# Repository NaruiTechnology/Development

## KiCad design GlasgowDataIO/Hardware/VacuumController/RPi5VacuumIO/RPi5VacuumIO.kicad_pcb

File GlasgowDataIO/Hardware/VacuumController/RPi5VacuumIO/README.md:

# RPi5 Vacuum Controller I/O board (rev A.1)

This is the interface board between a **Raspberry Pi** and the **FEI DB235 vacuum system**. The controller SBC is a **Raspberry Pi 4 Model B** (see `glasgow_service/docs/rpi-vacuum-shopping-list.md`); the board works unchanged on a **Raspberry Pi 5**, because it uses only the 40-pin header and every pin it uses has the same function on both models. The "RPi5" in the name is historical.

The board connects:

- the four pumps shown on the SBC Vacuum Controller dashboard: `MechanicalVacuumPump`, `TurboVacuumPump`, and the UH stage `UHVacuumPump_1` / `UHVacuumPump_2` (turbomolecular pumps);
- the vacuum gauges;
- the valves and pneumatic cylinders;
- the high-voltage permissive;
- the E-stop.

Step-by-step device wiring is in **[WIRING.md](WIRING.md)**.

The Pi runs `glasgow_service.sbc_vacuum_app`. This board gives it isolated, fail-safe I/O. The service talks to it through `glasgow_service/vacuum_io_board.py`. The whole board, the Pi and the DB235 are emulated in `glasgow_service.emulation`, so the controller can be tested without hardware (`python -m glasgow_service.emulation commission`; see `glasgow_service/docs/vacuum-emulator.md`).

```
 Raspberry Pi 4B/5 ─40-way ribbon─> J3 ─┬─ I2C ─ MCP23017 0x20 ─┬─ ULN2803A ─ K1..K8 relays  ─> pump / HV permissive contacts
                                       │                       └─ AO3400A x8 ─ V1..V8        ─> 24 V valve & cylinder solenoids
                                       ├─ I2C ─ MCP23017 0x21 ─── TLP291-4 x4 ─ DI1..DI16    <─ pump status, valve/cylinder switches
                                       ├─ I2C ─ ADS1115 x2 ─────── 68k/22k ─── AI1..AI8      <─ 0-10 V gauges, pump analog outputs
                                       ├─ UART0 ─ MAX3485 ──────── RS-485                    <─> turbo / gauge controller
                                       ├─ UART4 ─ MAX3232 ──────── RS-232                    <─> gauge controller
                                       └─ GPIO19 heartbeat ─ charge pump ─ K10 ─┐
 24 VDC ─ fuse ─ K9 (E-stop loop J2) ─ +24V_ESTOP ──────────────────────────────┴─ +24V_SAFE ─> solenoids, relay coils
```

## Channel counts

| Function | Channels | Hardware |
|---|---|---|
| Relay outputs | 8 × SPDT, 10 A contacts, COM/NO/NC on pluggable terminals | Omron G5LE-1 24 V, driven by ULN2803A |
| Solenoid outputs | 8 × 24 V low-side switches, up to 1 A each (fused 4 A total), flyback diodes, LED per channel | AO3400A MOSFETs |
| Digital inputs | 16 × opto-isolated 24 V, 4 groups with separate commons, LED per channel | TLP291-4 |
| Analog inputs | 8 × 0–10.5 V, 16-bit, clamped, about 90 Hz filter | ADS1115 × 2 |
| Serial | 1 × RS-485 (termination jumper, fail-safe bias, TVS); 1 × RS-232 | MAX3485, MAX3232 |
| Safety | E-stop loop input, heartbeat watchdog, rail status readback to the Pi | K9, K10, TLP291-4 |

## Channel map (matches the software)

The pumps, their order and their A/B channels are exactly those of `glasgow_service` and `vacuumSystem.json`, as shown on the SBC Vacuum Controller dashboard. The cascade is: `MechanicalVacuumPump` → `TurboVacuumPump` → the UH pump group (`UHVacuumPump_1`, `UHVacuumPump_2`).

| Software device | Output (A) → relay | Ready input (B) → DI | Fault input | Gauge (numeric value) | Speed / analog | Serial |
|---|---|---|---|---|---|---|
| `MechanicalVacuumPump` | A0 → **K1** | B0 → **DI1** (running / pressure OK) | DI5 | AI1 (fore-line Pirani) | – | – |
| `TurboVacuumPump` | A1 → **K2** | B1 → **DI2** (at normal speed) | DI6 | AI2 (chamber gauge) | AI5 | RS-485 J4, address 1 |
| `UHVacuumPump_1` (turbo) | A2 → **K3** | B2 → **DI3** (at normal speed) | DI7 | AI3 | AI6 | RS-485 J4, address 2 |
| `UHVacuumPump_2` (turbo) | A3 → **K4** | B3 → **DI4** (at normal speed) | DI8 | AI4 | AI7 | RS-485 J4, address 3 |
| `HighVoltageTransformer` | A4 → **K5** (HV permissive) | – | – | – | – | – |

The same map is printed on the back silkscreen. It is also in `GlasgowDataIO/Json/vacuumSystem.rpi5-io.example.json`.

### Remaining channels

| Channel | Suggested use |
|---|---|
| K6 | Full-range / cold-cathode gauge HV on |
| K7, K8 | Spare (for example an alarm beacon) |
| V1 | Roughing / fore-line valve (mechanical pump → turbo fore-lines) |
| V2 | Chamber gate valve (TurboVacuumPump inlet), pneumatic |
| V3 | Vent valve (dry N2) |
| V4 | UH stage isolation valve 1 (UHVacuumPump_1 inlet), pneumatic |
| V5 | UH stage isolation valve 2 (UHVacuumPump_2 inlet), pneumatic |
| V6 | Bypass / chamber roughing valve |
| V7 | Pneumatic cylinder (for example a load-lock or clamp) |
| V8 | Spare |
| DI9, DI10 | V2 open / closed position switches |
| DI11, DI12 | V4 open / closed position switches |
| DI13 | Chamber door closed |
| DI14 | Compressed air OK |
| DI15 | N2 vent gas OK |
| DI16 | Cooling water flow OK |
| AI8 | Spare |

The controller software sequences the pumps and the HV permissive (A0–A4, B0–B3, the per-pump gauges), and acts on the fault inputs (`SBC.Faults`), the E-stop and output-rail status (GPIO5/6), the keep-alive and expander resets. All 16 inputs, the relays and the solenoids are reported in `GET /vacuum` → `board`. The per-pump isolation valves V1, V2, V4 and V5 are driven by the controller (`SBC.Valves`: open exactly while that pump is ready, see `glasgow_service/docs/sbc-vacuum-controller.md`). The vent, bypass, cylinder and utility channels are wired and readable, but not sequenced yet.

## Fail-safe behaviour

| Condition | Result |
|---|---|
| Pi off, booting, or the service not started | GPIO22 is low, so both MCP23017s are held in reset. Every driver input is pulled down, and all relays and solenoids are **off**. |
| Pi or service hangs, crashes or reboots | The GPIO19 heartbeat stops. The charge pump blocks DC, so a pin stuck high or low looks the same. K10 drops in about 100 ms and **+24V_SAFE is removed**: all solenoids and every relay on the SAFE rail go off. |
| The service is alive but its control loop stops polling | The driver's keep-alive stops the heartbeat after 3 s, with the same result as above. |
| E-stop loop opened | K9 drops and **+24V_ESTOP and +24V_SAFE are both removed**. That means everything, including K1. |
| Rail status | GPIO5 (`ESTOP_OK_N`) and GPIO6 (`SAFE_OK_N`) let the software see both rails. |

**JP1–JP8** choose each relay coil's rail. By default K1 (the mechanical pump) runs from +24V_ESTOP, so the backing pump keeps running if the Pi hangs. When the service process exits (crash or restart) R10 resets the expanders and K1 drops as well, unless IO_RESET_N stays high (see `glasgow_service/docs/vacuum-24x7-commissioning.md`). K2–K8 run from +24V_SAFE. Move a jumper (cut the 1–2 bridge, bridge 2–3) to change a channel.

Valves must be **normally closed** (spring return) for "rail off = safe" to hold. If a normally-open valve is used, its safe state is open; check that this is acceptable.

K9 is a general-purpose relay, not a certified safety relay. For a category-rated E-stop, wire the output contacts of a safety relay (for example Pilz PNOZ or Phoenix PSR) into J2, and let that safety relay also remove power from the tool's own pump controllers.

Relay contacts are for the **permissive / remote-start inputs** of the tool's own pump controllers. They are not for switching pump motor mains. The PCB is laid out for low-voltage wiring.

## Connectors

| Ref | Where | Pins |
|---|---|---|
| J1 | left edge, Phoenix MSTBA 5.08 | `+24V`, `0V`. 24 VDC 2–4 A (DIN-rail PSU) |
| J2 | left edge, Phoenix MC 3.5 | E-stop NC loop: `ESTOP` (+24V_AUX out) and `LOOP` (return to K9 coil) |
| J3 | 2×20 box header | Ribbon to the Pi 40-pin header (pin 1 to pin 1). The Pi's 5 V pins are **not** connected, so power the Pi from its own USB-C supply |
| J11–J18 | top edge, MSTBA 5.08 | K1–K8 `COM`, `NO`, `NC` |
| J21–J24 | bottom edge, MC 3.5 | Two solenoids per connector: `+24`, `Vn-`, `+24`, `Vn+1-` |
| J31–J34 | bottom edge, MC 3.5 | Four inputs, then `COM` (0 V of that group), then `+24` (sensor supply, 0.5 A PTC). An input is active when 24 V is applied between DIn and COM |
| J41, J42 | right edge, MC 3.5 | `AIn` / `0V` pairs, 0–10.5 V |
| J4 | right edge, MC 3.5 | RS-485 `A`, `B`, `GND`. Bridge JP9 for 120 Ω termination |
| J5 | right edge, MC 3.5 | RS-232 `TXD` (out), `RXD` (in), `GND` |

## Raspberry Pi pins used

| BCM | Header pin | Function |
|---|---|---|
| 2 / 3 | 3 / 5 | I2C1 SDA / SCL |
| 14 / 15 | 8 / 10 | UART0 TX / RX → RS-485 |
| 18 | 12 | RS-485 driver enable |
| 12 / 13 | 32 / 33 | RS-232 TX / RX: UART5 on the Pi 4B (`dtoverlay=uart5`), UART4 on the Pi 5 (`dtoverlay=uart4-pi5`) |
| 19 | 35 | Watchdog heartbeat (1 kHz PWM) |
| 22 | 15 | `IO_RESET_N` (expanders held in reset while low) |
| 27 | 13 | Input change interrupt |
| 23 | 16 | ADC ALERT/RDY |
| 5 / 6 | 29 / 31 | `ESTOP_OK_N` / `SAFE_OK_N` (low = OK) |
| 26 | 37 | RUN LED |

Add to `/boot/firmware/config.txt`:

| Raspberry Pi 4 Model B | Raspberry Pi 5 |
|---|---|
| `dtparam=i2c_arm=on` | `dtparam=i2c_arm=on` |
| `enable_uart=1` | `enable_uart=1` |
| `dtoverlay=disable-bt` (full PL011 on GPIO14/15 for RS-485) | – |
| `dtoverlay=uart5` (RS-232, usually `/dev/ttyAMA1`) | `dtoverlay=uart4-pi5` (RS-232, `/dev/ttyAMA4`) |

## Software configuration

In `vacuumSystem.json`, replace the `SBC.GPIO` map with a board map. The complete example is `GlasgowDataIO/Json/vacuumSystem.rpi5-io.example.json`:

```json
"SBC": {
  "Id": "rpi-vacuum-io",
  "Board": "RPi5VacuumIO-A",
  "PiModel": "4B",
  "Channels": {"A0": "K1", "A1": "K2", "A2": "K3", "A3": "K4", "A4": "K5",
               "B0": "DI1", "B1": "DI2", "B2": "DI3", "B3": "DI4"},
  "Faults":   {"B0": "DI5", "B1": "DI6", "B2": "DI7", "B3": "DI8"},
  "Serial":   {"RS485": "/dev/ttyAMA0", "RS232": "/dev/ttyAMA1"},
  "Gauges": {"B0": {"AIN": "AI1", "Law": "log", "Slope": 1.0,   "Offset": -5.5},
             "B1": {"AIN": "AI2", "Law": "log", "Slope": 1.667, "Offset": -11.33},
             "B2": {"AIN": "AI3", "Law": "log", "Slope": 1.667, "Offset": -11.33},
             "B3": {"AIN": "AI4", "Law": "log", "Slope": 1.667, "Offset": -11.33}}
}
```

`Law: "log"` computes p = 10^(Slope·U + Offset). The example values are the Pfeiffer PKR 251 law in mbar. `Law: "linear"` computes p = Slope·U + Offset. Readings outside 0.5–10 V are reported as unknown (sensor error or not connected). `"IsProduction": false` runs the driver on the emulator instead of the board (the example config ships that way); set `"IsProduction": true` on the controller Pi for commissioning and production, then restart the service. Add `"Interlock": true` to a gauge to also require its pressure to be at or below the pump's `value` before the next stage starts. `Faults` are optional "healthy = ON" inputs: an open fault input stops that pump, raises an alarm and latches the cascade until `POST /vacuum/resume`. Install the extras with `pip install -e '.[sbc]'`, which adds `smbus2` and `pyserial`; the GPIO backend is `python3-lgpio` (works on both Pi models).

## PCB and files

The board is 195 × 160 mm, 2 layers, 1.6 mm FR-4, 1 oz copper, with a GND pour on both sides. Tracks are 0.2 mm for signals (0.15 mm minimum clearance), 0.8 mm for the 24 V rails, 0.6 mm for coil and solenoid lines, and 1.0 mm for relay contacts (with 1.0 mm clearance). Vias are 0.6/0.3 mm. All of this is within any standard 2-layer service.

| Path | Content |
|---|---|
| `RPi5VacuumIO.kicad_pro/.kicad_sch/.kicad_pcb` | KiCad project. The board is KiCad 10 format and is edited in KiCad 10 |
| `fab/RPi5VacuumIO-gerbers-<rev>.zip` | **Upload to the board house** (Gerber X2, Excellon, job file with stackup and finish) |
| `fab/README.md` | Fabrication and assembly notes: board spec, hole table, release checks, review items |
| `fab/assembly/` | BOM (with MPNs and mating-plug part numbers), pick-and-place, assembly drawing |
| `fab/*-ipc2581.xml`, `fab/*-odb.zip`, `fab/*-ipcd356.ipc` | IPC-2581, ODB++, electrical-test netlist |
| `fab/*-schematic.pdf`, `fab/*.step`, `fab/reports/` | Schematic, 3D model, ERC/DRC reports |
| `fab/RPi5VacuumIO-manufacturing-<rev>.zip`, `fab/SHA256SUMS` | Everything above in one archive, with checksums |
| `tools/` | `make_fab_kicad10.sh` / `.ps1` (fab package), `prodprep.py`, `fabnotes.py`, `sync_from_schematic.py`; `design.py` and `build.sh` generated the original KiCad 7 layout |

Regenerate the package with KiCad 10 from this folder, on Windows with
`powershell -ExecutionPolicy Bypass -File .\tools\make_fab_kicad10.ps1` or on Linux/macOS with
`tools/make_fab_kicad10.sh` (`REV=A.2` to change the revision). Both refuse to write `fab/` unless
ERC has no errors and DRC has no errors, no unconnected items and no schematic/board mismatches.
`tools/build.sh` would rebuild the board from `design.py` and discard KiCad 10 edits, so it now
refuses to run on the KiCad 10 board.

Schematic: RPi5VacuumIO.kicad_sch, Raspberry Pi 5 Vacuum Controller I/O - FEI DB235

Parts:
C1: 47uF 50V; CP_Elec_8x10; MPN Panasonic EEE-FK1H470P
C2, C8, C9, C10, C11, C12, C13, C14, C15, C16, C17, C21, C22, C23, C24, C25, C26, C27, C28: 100nF; C_0805_2012Metric_Pad1.18x1.45mm_HandSolder; MPN 0805 100nF 50V X7R
C3: 10uF; C_0805_2012Metric_Pad1.18x1.45mm_HandSolder; MPN 0805 10uF 16V X5R
C4, C5: 1uF; C_0805_2012Metric_Pad1.18x1.45mm_HandSolder; MPN 0805 1uF 25V X7R
C6, C7: 10uF; C_1210_3225Metric_Pad1.33x2.70mm_HandSolder; MPN 1210 10uF 50V X7R
D1: SS54; D_SMC; MPN SS54 (5 A 40 V Schottky, SMC)
D2: SMAJ33CA; D_SMA; MPN Littelfuse SMAJ33CA
D3, D10, D101, D102, D103, D104, D105, D106, D107, D108, D109, D110, D111, D112, D113, D114, D115, D116: GRN; LED_0805_2012Metric_Pad1.15x1.40mm_HandSolder; MPN 0805 GRN LED
D4, D5, D121, D122, D123, D124, D125, D126, D127, D128, D129, D130, D131, D132, D133, D134, D135, D136: 1N4148W; D_SOD-123; MPN 1N4148W
D6, D61, D62, D63, D64, D65, D66, D67, D68: BAT54S; SOT-23; MPN BAT54S
D7, D8: SS34; D_SMA; MPN SS34 (3 A 40 V Schottky)
D9, D41, D42, D43, D44, D45, D46, D47, D48: YEL; LED_0805_2012Metric_Pad1.15x1.40mm_HandSolder; MPN 0805 YEL LED
D11: BLU; LED_0805_2012Metric_Pad1.15x1.40mm_HandSolder; MPN 0805 BLU LED
D12, D13: SMAJ12CA; D_SMA; MPN SMAJ12CA
D21, D22, D23, D24, D25, D26, D27, D28: RED; LED_0805_2012Metric_Pad1.15x1.40mm_HandSolder; MPN 0805 RED LED
D31, D32, D33, D34, D35, D36, D37, D38: SS14; D_SMA; MPN SS14 (1 A 40 V Schottky)
F1: 4A T; Fuse_Littelfuse_395Series; MPN Littelfuse 39214000000 (TR5 4 A slow)
F2: 0.5A 30V; Fuse_1812_4532Metric; MPN Littelfuse 1812L050/30DR
H1, H2, H3, H4: M3; MountingHole_3.2mm_M3
J1: 24VDC_IN; PhoenixContact_MSTBA_2,5_2-G-5,08_1x02_P5.08mm_Horizontal; MPN Phoenix 1757242 (MSTBA 2,5/2-G-5,08); p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
J2: ESTOP; PhoenixContact_MC_1,5_2-G-3.5_1x02_P3.50mm_Horizontal; MPN Phoenix 1844210; plug 1840366
J3: RPI5_40PIN; IDC-Header_2x20_P2.54mm_Vertical; MPN 2x20 2.54 mm shrouded box header + 40-w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
J4: RS485; PhoenixContact_MC_1,5_3-G-3.5_1x03_P3.50mm_Horizontal; MPN Phoenix 1844223; plug 1840379
J5: RS232; PhoenixContact_MC_1,5_3-G-3.5_1x03_P3.50mm_Horizontal; MPN Phoenix 1844223; plug 1840379
J11: RELAY1; PhoenixContact_MSTBA_2,5_3-G-5,08_1x03_P5.08mm_Horizontal; MPN Phoenix 1757255 (MSTBA 2,5/3-G-5,08); p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
J12: RELAY2; PhoenixContact_MSTBA_2,5_3-G-5,08_1x03_P5.08mm_Horizontal; MPN Phoenix 1757255 (MSTBA 2,5/3-G-5,08); p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
J13: RELAY3; PhoenixContact_MSTBA_2,5_3-G-5,08_1x03_P5.08mm_Horizontal; MPN Phoenix 1757255 (MSTBA 2,5/3-G-5,08); p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
J14: RELAY4; PhoenixContact_MSTBA_2,5_3-G-5,08_1x03_P5.08mm_Horizontal; MPN Phoenix 1757255 (MSTBA 2,5/3-G-5,08); p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
J15: RELAY5; PhoenixContact_MSTBA_2,5_3-G-5,08_1x03_P5.08mm_Horizontal; MPN Phoenix 1757255 (MSTBA 2,5/3-G-5,08); p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
J16: RELAY6; PhoenixContact_MSTBA_2,5_3-G-5,08_1x03_P5.08mm_Horizontal; MPN Phoenix 1757255 (MSTBA 2,5/3-G-5,08); p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
J17: RELAY7; PhoenixContact_MSTBA_2,5_3-G-5,08_1x03_P5.08mm_Horizontal; MPN Phoenix 1757255 (MSTBA 2,5/3-G-5,08); p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
J18: RELAY8; PhoenixContact_MSTBA_2,5_3-G-5,08_1x03_P5.08mm_Horizontal; MPN Phoenix 1757255 (MSTBA 2,5/3-G-5,08); p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
J21: SOL1-2; PhoenixContact_MC_1,5_4-G-3.5_1x04_P3.50mm_Horizontal; MPN Phoenix 1844236; plug 1840382
J22: SOL3-4; PhoenixContact_MC_1,5_4-G-3.5_1x04_P3.50mm_Horizontal; MPN Phoenix 1844236; plug 1840382
J23: SOL5-6; PhoenixContact_MC_1,5_4-G-3.5_1x04_P3.50mm_Horizontal; MPN Phoenix 1844236; plug 1840382
J24: SOL7-8; PhoenixContact_MC_1,5_4-G-3.5_1x04_P3.50mm_Horizontal; MPN Phoenix 1844236; plug 1840382
J31: DI1-4; PhoenixContact_MC_1,5_6-G-3.5_1x06_P3.50mm_Horizontal; MPN Phoenix 1844252 (MC 1,5/6-G-3,5); plug 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
J32: DI5-8; PhoenixContact_MC_1,5_6-G-3.5_1x06_P3.50mm_Horizontal; MPN Phoenix 1844252 (MC 1,5/6-G-3,5); plug 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
J33: DI9-12; PhoenixContact_MC_1,5_6-G-3.5_1x06_P3.50mm_Horizontal; MPN Phoenix 1844252 (MC 1,5/6-G-3,5); plug 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
J34: DI13-16; PhoenixContact_MC_1,5_6-G-3.5_1x06_P3.50mm_Horizontal; MPN Phoenix 1844252 (MC 1,5/6-G-3,5); plug 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
J41: AI1-4; PhoenixContact_MC_1,5_8-G-3.5_1x08_P3.50mm_Horizontal; MPN Phoenix 1844278 (MC 1,5/8-G-3,5); plug 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
J42: AI5-8; PhoenixContact_MC_1,5_8-G-3.5_1x08_P3.50mm_Horizontal; MPN Phoenix 1844278 (MC 1,5/8-G-3,5); plug 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
JP1, JP2, JP3, JP4, JP5, JP6, JP7, JP8: RAIL_SEL; SolderJumper-3_P1.3mm_Bridged12_RoundedPad1.0x1.5mm
JP9: TERM; SolderJumper-2_P1.3mm_Open_RoundedPad1.0x1.5mm
K1, K2, K3, K4, K5, K6, K7, K8, K9, K10: G5LE-1 24VDC; Relay_SPDT_Omron-G5LE-1; MPN Omron G5LE-1 DC24
Q1, Q2, Q3, Q4, Q5, Q6, Q7, Q8, Q9: AO3400A; SOT-23; MPN AOS AO3400A
R1, R4, R5, R31, R32, R33, R34, R35, R36, R37, R38, R61, R62, R63, R64, R65, R66, R67, R68, R101, R102, R103, R104, R105, R106, R107, R108, R109, R110, R111, R112, R113, R114, R115, R116: 4.7k; R_1206_3216Metric_Pad1.30x1.75mm_HandSolder; MPN SMD:R 4.7k 1%
R2, R41, R42, R43, R44, R45, R46, R47, R48: 100R; R_0805_2012Metric_Pad1.20x1.40mm_HandSolder; MPN SMD:R 100R 1%
R3, R21, R22, R23, R24, R25, R26, R27, R28, R51, R52, R53, R54, R55, R56, R57, R58: 100k; R_0805_2012Metric_Pad1.20x1.40mm_HandSolder; MPN SMD:R 100k 1%
R6, R7: 10k; R_1206_3216Metric_Pad1.30x1.75mm_HandSolder; MPN SMD:R 10k 1%
R8, R9, R10, R12, R13, R14, R121, R122, R123, R124, R125, R126, R127, R128, R129, R130, R131, R132, R133, R134, R135, R136: 10k; R_0805_2012Metric_Pad1.20x1.40mm_HandSolder; MPN SMD:R 10k 1%
R11: 1k; R_0805_2012Metric_Pad1.20x1.40mm_HandSolder; MPN SMD:R 1k 1%
R15, R16: 680R; R_0805_2012Metric_Pad1.20x1.40mm_HandSolder; MPN SMD:R 680R 1%
R17: 120R; R_0805_2012Metric_Pad1.20x1.40mm_HandSolder; MPN SMD:R 120R 1%
R141, R142, R143, R144, R145, R146, R147, R148: 68k; R_0805_2012Metric_Pad1.20x1.40mm_HandSolder; MPN SMD:R 68k 1%
R151, R152, R153, R154, R155, R156, R157, R158: 22k; R_0805_2012Metric_Pad1.20x1.40mm_HandSolder; MPN SMD:R 22k 1%
U1, U3: MCP23017; SOIC-28W_7.5x17.9mm_P1.27mm; MPN Microchip MCP23017-E/SO
U2: ULN2803A; SOIC-18W_7.5x11.6mm_P1.27mm; MPN TI ULN2803ADWR
U5, U6, U7, U8, U13: TLP291-4; SOIC-16_4.55x10.3mm_P1.27mm; MPN Toshiba TLP291-4(GB-TP,E)
U9, U10: ADS1115; TSSOP-10_3x3mm_P0.5mm; MPN TI ADS1115IDGSR
U11: MAX3485; SOIC-8_3.9x4.9mm_P1.27mm; MPN MAX3485ESA+ (or SP3485EN)
U12: MAX3232; SOIC-16_3.9x9.9mm_P1.27mm; MPN TI MAX3232ECDR

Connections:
/+3V3: C3.1, C8.1, C9.1, C10.1, C11.1, C12.1, C17.1, D61.2 (K), D62.2 (K), D63.2 (K), D64.2 (K), D65.2 (K), D66.2 (K), D67.2 (K), D68.2 (K), J3.1, J3.17, R8.1, R9.1, R12.1, R13.1, R15.1, R121.1, R122.1, R123.1, R124.1, R125.1, R126.1, R127.1, R128.1, R129.1, R130.1, R131.1, R132.1, R133.1, R134.1, R135.1, R136.1, U1.9 (VDD), U3.9 (VDD), U3.15 (A0), U9.8 (VDD), U10.1 (ADDR), U10.8 (VDD), U11.8 (VCC), U12.16 (VCC)
/+24V: C1.1, C2.1, D1.1 (K), D2.1 (A1), F2.1, K9.1, R1.1
/+24V_AUX: F2.2, J2.1, J31.6, J32.6, J33.6, J34.6
/+24V_ESTOP: C6.1, D5.1 (K), D7.1 (K), JP1.1 (A), JP2.3 (B), JP3.3 (B), JP4.3 (B), JP5.3 (B), JP6.3 (B), JP7.3 (B), JP8.3 (B), K9.4, K10.1, K10.5, R4.1, R6.1, U2.10 (COM)
/+24V_F: D1.2 (A), F1.2
/+24V_RAW: F1.1, J1.1
/+24V_SAFE: C7.1, D8.1 (K), D31.1 (K), D32.1 (K), D33.1 (K), D34.1 (K), D35.1 (K), D36.1 (K), D37.1 (K), D38.1 (K), J21.1, J21.3, J22.1, J22.3, J23.1, J23.3, J24.1, J24.3, JP1.3 (B), JP2.1 (A), JP3.1 (A), JP4.1 (A), JP5.1 (A), JP6.1 (A), JP7.1 (A), JP8.1 (A), K10.4, R5.1, R7.1, R61.1, R62.1, R63.1, R64.1, R65.1, R66.1, R67.1, R68.1
/ADC_ALRT: J3.16, R13.2, U9.2 (ALERT/RDY), U10.2 (ALERT/RDY)
/AI1: J41.1, R141.1
/AI2: J41.3, R142.1
/AI3: J41.5, R143.1
/AI4: J41.7, R144.1
/AI5: J42.1, R145.1
/AI6: J42.3, R146.1
/AI7: J42.5, R147.1
/AI8: J42.7, R148.1
/AI_S1: C21.1, D61.3 (COM), R141.2, R151.1, U9.4 (AIN0)
/AI_S2: C22.1, D62.3 (COM), R142.2, R152.1, U9.5 (AIN1)
/AI_S3: C23.1, D63.3 (COM), R143.2, R153.1, U9.6 (AIN2)
/AI_S4: C24.1, D64.3 (COM), R144.2, R154.1, U9.7 (AIN3)
/AI_S5: C25.1, D65.3 (COM), R145.2, R155.1, U10.4 (AIN0)
/AI_S6: C26.1, D66.3 (COM), R146.2, R156.1, U10.5 (AIN1)
/AI_S7: C27.1, D67.3 (COM), R147.2, R157.1, U10.6 (AIN2)
/AI_S8: C28.1, D68.3 (COM), R148.2, R158.1, U10.7 (AIN3)
/C1N: C13.2, U12.3 (C1-)
/C1P: C13.1, U12.1 (C1+)
/C2N: C14.2, U12.5 (C2-)
/C2P: C14.1, U12.4 (C2+)
/DI1: J31.1, R101.1
/DI2: J31.2, R102.1
/DI3: J31.3, R103.1
/DI4: J31.4, R104.1
/DI5: J32.1, R105.1
/DI6: J32.2, R106.1
/DI7: J32.3, R107.1
/DI8: J32.4, R108.1
/DI9: J33.1, R109.1
/DI10: J33.2, R110.1
/DI11: J33.3, R111.1
/DI12: J33.4, R112.1
/DI13: J34.1, R113.1
/DI14: J34.2, R114.1
/DI15: J34.3, R115.1
/DI16: J34.4, R116.1
/DI_A1: D101.1 (K), U5.1
/DI_A2: D102.1 (K), U5.3
/DI_A3: D103.1 (K), U5.5
/DI_A4: D104.1 (K), U5.7
/DI_A5: D105.1 (K), U6.1
/DI_A6: D106.1 (K), U6.3
/DI_A7: D107.1 (K), U6.5
/DI_A8: D108.1 (K), U6.7
/DI_A9: D109.1 (K), U7.1
/DI_A10: D110.1 (K), U7.3
/DI_A11: D111.1 (K), U7.5
/DI_A12: D112.1 (K), U7.7
/DI_A13: D113.1 (K), U8.1
/DI_A14: D114.1 (K), U8.3
/DI_A15: D115.1 (K), U8.5
/DI_A16: D116.1 (K), U8.7
/DI_COM1: D121.2 (A), D122.2 (A), D123.2 (A), D124.2 (A), J31.5, U5.2, U5.4, U5.6, U5.8
/DI_COM2: D125.2 (A), D126.2 (A), D127.2 (A), D128.2 (A), J32.5, U6.2, U6.4, U6.6, U6.8
/DI_COM3: D129.2 (A), D130.2 (A), D131.2 (A), D132.2 (A), J33.5, U7.2, U7.4, U7.6, U7.8
/DI_COM4: D133.2 (A), D134.2 (A), D135.2 (A), D136.2 (A), J34.5, U8.2, U8.4, U8.6, U8.8
/DI_INT: J3.13, R12.2, U3.20 (INTA)
/DI_L1: D101.2 (A), D121.1 (K), R101.2
/DI_L2: D102.2 (A), D122.1 (K), R102.2
/DI_L3: D103.2 (A), D123.1 (K), R103.2
/DI_L4: D104.2 (A), D124.1 (K), R104.2
/DI_L5: D105.2 (A), D125.1 (K), R105.2
/DI_L6: D106.2 (A), D126.1 (K), R106.2
/DI_L7: D107.2 (A), D127.1 (K), R107.2
/DI_L8: D108.2 (A), D128.1 (K), R108.2
/DI_L9: D109.2 (A), D129.1 (K), R109.2
/DI_L10: D110.2 (A), D130.1 (K), R110.2
/DI_L11: D111.2 (A), D131.1 (K), R111.2
/DI_L12: D112.2 (A), D132.1 (K), R112.2
/DI_L13: D113.2 (A), D133.1 (K), R113.2
/DI_L14: D114.2 (A), D134.1 (K), R114.2
/DI_L15: D115.2 (A), D135.1 (K), R115.2
/DI_L16: D116.2 (A), D136.1 (K), R116.2
/DI_N1: R121.2, U3.21 (GPA0), U5.16
/DI_N2: R122.2, U3.22 (GPA1), U5.14
/DI_N3: R123.2, U3.23 (GPA2), U5.12
/DI_N4: R124.2, U3.24 (GPA3), U5.10
/DI_N5: R125.2, U3.25 (GPA4), U6.16
/DI_N6: R126.2, U3.26 (GPA5), U6.14
/DI_N7: R127.2, U3.27 (GPA6), U6.12
/DI_N8: R128.2, U3.28 (GPA7), U6.10
/DI_N9: R129.2, U3.1 (GPB0), U7.16
/DI_N10: R130.2, U3.2 (GPB1), U7.14
/DI_N11: R131.2, U3.3 (GPB2), U7.12
/DI_N12: R132.2, U3.4 (GPB3), U7.10
/DI_N13: R133.2, U3.5 (GPB4), U8.16
/DI_N14: R134.2, U3.6 (GPB5), U8.14
/DI_N15: R135.2, U3.7 (GPB6), U8.12
/DI_N16: R136.2, U3.8 (GPB7), U8.10
/ESTOP_OK_N: J3.29, R8.2, U13.16
/ESTOP_RET: D4.1 (K), J2.2, K9.5
/GND: C1.2, C2.2, C3.2, C5.2, C6.2, C7.2, C8.2, C9.2, C10.2, C11.2, C12.2, C15.2, C16.2, C17.2, C21.2, C22.2, C23.2, C24.2, C25.2, C26.2, C27.2, C28.2, D2.2 (A2), D3.1 (K), D4.2 (A), D6.1 (A), D7.2 (A), D8.2 (A), D9.1 (K), D10.1 (K), D11.1 (K), D12.2 (A2), D13.2 (A2), D61.1 (A), D62.1 (A), D63.1 (A), D64.1 (A), D65.1 (A), D66.1 (A), D67.1 (A), D68.1 (A), J1.2, J3.6, J3.9, J3.14, J3.20, J3.25, J3.30, J3.34, J3.39, J4.3, J5.3, J41.2, J41.4, J41.6, J41.8, J42.2, J42.4, J42.6, J42.8, K9.2, Q1.2 (S), Q2.2 (S), Q3.2 (S), Q4.2 (S), Q5.2 (S), Q6.2 (S), Q7.2 (S), Q8.2 (S), Q9.2 (S), R3.2, R10.2, R14.2, R16.2, R21.2, R22.2, R23.2, R24.2, R25.2, R26.2, R27.2, R28.2, R51.2, R52.2, R53.2, R54.2, R55.2, R56.2, R57.2, R58.2, R151.2, R152.2, R153.2, R154.2, R155.2, R156.2, R157.2, R158.2, U1.10 (VSS), U1.15 (A0), U1.16 (A1), U1.17 (A2), U2.9 (GND), U3.10 (VSS), U3.16 (A1), U3.17 (A2), U5.9, U5.11, U5.13, U5.15, U6.9, U6.11, U6.13, U6.15, U7.9, U7.11, U7.13, U7.15, U8.9, U8.11, U8.13, U8.15, U9.1 (ADDR), U9.3 (GND), U10.3 (GND), U11.5 (GND), U12.10 (T2IN), U12.15 (GND), U13.2, U13.4, U13.5, U13.6, U13.7, U13.8, U13.9, U13.11, U13.13, U13.15
/IO_RESET_N: J3.15, R10.1, U1.18 (~RESET), U3.18 (~RESET)
/K1_COM: J11.1, K1.1
/K1_NC: J11.3, K1.3
/K1_NO: J11.2, K1.4
/K2_COM: J12.1, K2.1
/K2_NC: J12.3, K2.3
/K2_NO: J12.2, K2.4
/K3_COM: J13.1, K3.1
/K3_NC: J13.3, K3.3
/K3_NO: J13.2, K3.4
/K4_COM: J14.1, K4.1
/K4_NC: J14.3, K4.3
/K4_NO: J14.2, K4.4
/K5_COM: J15.1, K5.1
/K5_NC: J15.3, K5.3
/K5_NO: J15.2, K5.4
/K6_COM: J16.1, K6.1
/K6_NC: J16.3, K6.3
/K6_NO: J16.2, K6.4
/K7_COM: J17.1, K7.1
/K7_NC: J17.3, K7.3
/K7_NO: J17.2, K7.4
/K8_COM: J18.1, K8.1
/K8_NC: J18.3, K8.3
/K8_NO: J18.2, K8.4
/LED_24V: D3.2 (A), R1.2
/LED_EST: D9.2 (A), R4.2
/LED_RUN: D11.2 (A), R11.2
/LED_SAFE: D10.2 (A), R5.2
/RLY_IN1: R21.1, U1.21 (GPA0), U2.1 (I1)
/RLY_IN2: R22.1, U1.22 (GPA1), U2.2 (I2)
/RLY_IN3: R23.1, U1.23 (GPA2), U2.3 (I3)
/RLY_IN4: R24.1, U1.24 (GPA3), U2.4 (I4)
/RLY_IN5: R25.1, U1.25 (GPA4), U2.5 (I5)
/RLY_IN6: R26.1, U1.26 (GPA5), U2.6 (I6)
/RLY_IN7: R27.1, U1.27 (GPA6), U2.7 (I7)
/RLY_IN8: R28.1, U1.28 (GPA7), U2.8 (I8)
/RLY_L1: D21.1 (K), K1.2, U2.18 (O1)
/RLY_L2: D22.1 (K), K2.2, U2.17 (O2)
/RLY_L3: D23.1 (K), K3.2, U2.16 (O3)
/RLY_L4: D24.1 (K), K4.2, U2.15 (O4)
/RLY_L5: D25.1 (K), K5.2, U2.14 (O5)
/RLY_L6: D26.1 (K), K6.2, U2.13 (O6)
/RLY_L7: D27.1 (K), K7.2, U2.12 (O7)
/RLY_L8: D28.1 (K), K8.2, U2.11 (O8)
/RLY_LED1: D21.2 (A), R31.2
/RLY_LED2: D22.2 (A), R32.2
/RLY_LED3: D23.2 (A), R33.2
/RLY_LED4: D24.2 (A), R34.2
/RLY_LED5: D25.2 (A), R35.2
/RLY_LED6: D26.2 (A), R36.2
/RLY_LED7: D27.2 (A), R37.2
/RLY_LED8: D28.2 (A), R38.2
/RLY_V1: JP1.2 (C), K1.5, R31.1
/RLY_V2: JP2.2 (C), K2.5, R32.1
/RLY_V3: JP3.2 (C), K3.5, R33.1
/RLY_V4: JP4.2 (C), K4.5, R34.1
/RLY_V5: JP5.2 (C), K5.5, R35.1
/RLY_V6: JP6.2 (C), K6.5, R36.1
/RLY_V7: JP7.2 (C), K7.5, R37.1
/RLY_V8: JP8.2 (C), K8.5, R38.1
/RS232_RX: J3.33, U12.12 (R1OUT)
/RS232_RXD: J5.2, U12.13 (R1IN)
/RS232_TX: J3.32, U12.11 (T1IN)
/RS232_TXD: J5.1, U12.14 (T1OUT)
/RS485_A: D12.1 (A1), J4.1, R15.2, R17.1, U11.6 (A)
/RS485_B: D13.1 (A1), J4.2, JP9.2 (B), R16.1, U11.7 (B)
/RS485_DE: J3.12, R14.1, U11.2 (~RE), U11.3 (DE)
/RS485_RX: J3.10, U11.1 (RO)
/RS485_T: JP9.1 (A), R17.2
/RS485_TX: J3.8, U11.4 (DI)
/RUN_LED: J3.37, R11.1
/SAFE_OK_N: J3.31, R9.2, U13.14
/SCL: J3.5, U1.12 (SCK), U3.12 (SCK), U9.10 (SCL), U10.10 (SCL)
/SDA: J3.3, U1.13 (SDA), U3.13 (SDA), U9.9 (SDA), U10.9 (SDA)
/SOL_D1: D31.2 (A), D41.1 (K), J21.2, Q1.3 (D)
/SOL_D2: D32.2 (A), D42.1 (K), J21.4, Q2.3 (D)
/SOL_D3: D33.2 (A), D43.1 (K), J22.2, Q3.3 (D)
/SOL_D4: D34.2 (A), D44.1 (K), J22.4, Q4.3 (D)
/SOL_D5: D35.2 (A), D45.1 (K), J23.2, Q5.3 (D)
/SOL_D6: D36.2 (A), D46.1 (K), J23.4, Q6.3 (D)
/SOL_D7: D37.2 (A), D47.1 (K), J24.2, Q7.3 (D)
/SOL_D8: D38.2 (A), D48.1 (K), J24.4, Q8.3 (D)
/SOL_G1: Q1.1 (G), R41.2, R51.1
/SOL_G2: Q2.1 (G), R42.2, R52.1
/SOL_G3: Q3.1 (G), R43.2, R53.1
/SOL_G4: Q4.1 (G), R44.2, R54.1
/SOL_G5: Q5.1 (G), R45.2, R55.1
/SOL_G6: Q6.1 (G), R46.2, R56.1
/SOL_G7: Q7.1 (G), R47.2, R57.1
/SOL_G8: Q8.1 (G), R48.2, R58.1
/SOL_IN1: R41.1, U1.1 (GPB0)
/SOL_IN2: R42.1, U1.2 (GPB1)
/SOL_IN3: R43.1, U1.3 (GPB2)
/SOL_IN4: R44.1, U1.4 (GPB3)
/SOL_IN5: R45.1, U1.5 (GPB4)
/SOL_IN6: R46.1, U1.6 (GPB5)
/SOL_IN7: R47.1, U1.7 (GPB6)
/SOL_IN8: R48.1, U1.8 (GPB7)
/SOL_LED1: D41.2 (A), R61.2
/SOL_LED2: D42.2 (A), R62.2
/SOL_LED3: D43.2 (A), R63.2
/SOL_LED4: D44.2 (A), R64.2
/SOL_LED5: D45.2 (A), R65.2
/SOL_LED6: D46.2 (A), R66.2
/SOL_LED7: D47.2 (A), R67.2
/SOL_LED8: D48.2 (A), R68.2
/ST_A1: R6.2, U13.1
/ST_A2: R7.2, U13.3
/VSN: C16.1, U12.6 (VS-)
/VSP: C15.1, U12.2 (VS+)
/WDT_AC: C4.2, D6.3 (COM)
/WDT_DRAIN: D5.2 (A), K10.2, Q9.3 (D)
/WDT_GATE: C5.1, D6.2 (K), Q9.1 (G), R3.1
/WDT_HB: J3.35, R2.1
/WDT_HB_R: C4.1, R2.2

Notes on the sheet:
POWER INPUT 24 V
E-STOP + WATCHDOG OUTPUT RAILS
RASPBERRY PI 5 HEADER
OUTPUT EXPANDER + RELAY DRIVER
RELAY K1
RELAY K2
RELAY K3
RELAY K4
RELAY K5
RELAY K6
RELAY K7
RELAY K8
SOLENOID DRIVERS (valves, cylinders)
INPUT EXPANDER
ISOLATED INPUTS 1-4
ISOLATED INPUTS 5-8
ISOLATED INPUTS 9-12
ISOLATED INPUTS 13-16
GAUGE / ANALOG INPUTS 0-10 V
RS-485 (turbo pump controllers, multi-drop)
RS-232
MECHANICAL
DESIGN NOTES 1. Output power: +24V -> K9 (closed only while the E-stop loop J2 is closed) -> +24V_ESTOP -> K10 (closed only while the Pi toggles GPIO19 at >= 500 Hz; charge pump blocks DC so a hung or rebooting Pi drops it in ~100 ms) -> +24V_SAFE. 2. Solenoid valves/cylinders are powered from +24V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

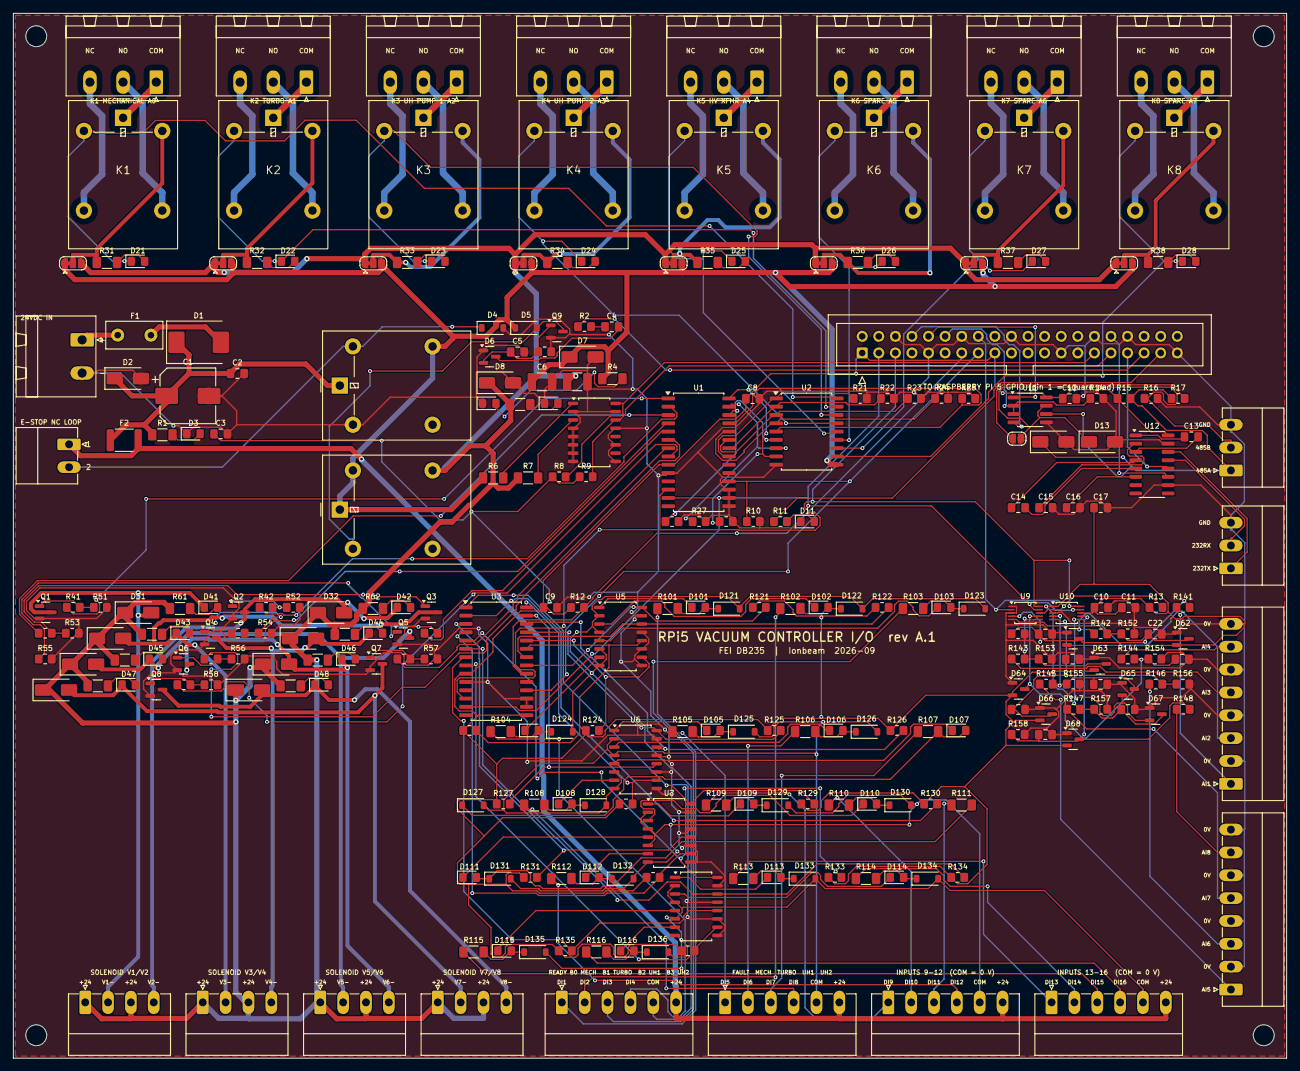
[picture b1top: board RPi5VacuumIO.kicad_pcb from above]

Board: 2 copper layers, 195.0 x 160.0 mm, 276 parts (0 on the bottom side), 216 nets.

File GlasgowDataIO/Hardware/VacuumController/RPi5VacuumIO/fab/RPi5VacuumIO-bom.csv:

Qty,References,Value,Footprint,Manufacturer part / spec,Notes
1,J1,24VDC_IN,"PhoenixContact_MSTBA_2,5_2-G-5,08_1x02_P5.08mm_Horizontal","Phoenix 1757242 (MSTBA 2,5/2-G-5,08); plug 1757019",24 V DC field supply input
1,F1,4A T,Fuse_Littelfuse_395Series,Littelfuse 39214000000 (TR5 4 A slow),Main fuse
1,D1,SS54,D_SMC,"SS54 (5 A 40 V Schottky, SMC)",Reverse-polarity protection
1,D2,SMAJ33CA,D_SMA,Littelfuse SMAJ33CA,24 V rail surge clamp
1,C1,47uF 50V,CP_Elec_8x10,Panasonic EEE-FK1H470P,24 V bulk
19,C2 C8 C9 C10 C11 C12 C13 C14 C15 C16 C17 C21 C22 C23 C24 C25 C26 C27 C28,100nF,C_0805_2012Metric_Pad1.18x1.45mm_HandSolder,0805 100nF 50V X7R,
1,F2,0.5A 30V,Fuse_1812_4532Metric,Littelfuse 1812L050/30DR,Sensor / E-stop loop supply
35,R1 R4 R5 R31 R32 R33 R34 R35 R36 R37 R38 R61 R62 R63 R64 R65 R66 R67 R68 R101 R102 R103 R104 R105 R106 R107 R108 R109 R110 R111 R112 R113 R114 R115 R116,4.7k,R_1206_3216Metric_Pad1.30x1.75mm_HandSolder,SMD:R 4.7k 1%,
18,D3 D10 D101 D102 D103 D104 D105 D106 D107 D108 D109 D110 D111 D112 D113 D114 D115 D116,GRN,LED_0805_2012Metric_Pad1.15x1.40mm_HandSolder,0805 GRN LED,24 V present
1,C3,10uF,C_0805_2012Metric_Pad1.18x1.45mm_HandSolder,0805 10uF 16V X5R,3V3 bulk (3V3 comes from the Pi)
1,J2,ESTOP,"PhoenixContact_MC_1,5_2-G-3.5_1x02_P3.50mm_Horizontal",Phoenix 1844210; plug 1840366,E-stop NC loop (or safety-relay output)
10,K1 K2 K3 K4 K5 K6 K7 K8 K9 K10,G5LE-1 24VDC,Relay_SPDT_Omron-G5LE-1,Omron G5LE-1 DC24,E-stop rail relay
18,D4 D5 D121 D122 D123 D124 D125 D126 D127 D128 D129 D130 D131 D132 D133 D134 D135 D136,1N4148W,D_SOD-123,1N4148W,K9 coil flyback
9,Q1 Q2 Q3 Q4 Q5 Q6 Q7 Q8 Q9,AO3400A,SOT-23,AOS AO3400A,K10 coil driver
9,R2 R41 R42 R43 R44 R45 R46 R47 R48,100R,R_0805_2012Metric_Pad1.20x1.40mm_HandSolder,SMD:R 100R 1%,Heartbeat series
2,C4 C5,1uF,C_0805_2012Metric_Pad1.18x1.45mm_HandSolder,0805 1uF 25V X7R,Charge pump coupling (blocks DC: stuck pin = trip)
9,D6 D61 D62 D63 D64 D65 D66 D67 D68,BAT54S,SOT-23,BAT54S,Charge pump diodes
17,R3 R21 R22 R23 R24 R25 R26 R27 R28 R51 R52 R53 R54 R55 R56 R57 R58,100k,R_0805_2012Metric_Pad1.20x1.40mm_HandSolder,SMD:R 100k 1%,"Watchdog bleed, ~100 ms drop-out"
2,D7 D8,SS34,D_SMA,SS34 (3 A 40 V Schottky),ESTOP rail freewheel
2,C6 C7,10uF,C_1210_3225Metric_Pad1.33x2.70mm_HandSolder,1210 10uF 50V X7R,
9,D9 D41 D42 D43 D44 D45 D46 D47 D48,YEL,LED_0805_2012Metric_Pad1.15x1.40mm_HandSolder,0805 YEL LED,E-stop rail live
5,U5 U6 U7 U8 U13,TLP291-4,SOIC-16_4.55x10.3mm_P1.27mm,"Toshiba TLP291-4(GB-TP,E)",Rail status to Pi GPIO5/6
2,R6 R7,10k,R_1206_3216Metric_Pad1.30x1.75mm_HandSolder,SMD:R 10k 1%,
22,R8 R9 R10 R12 R13 R14 R121 R122 R123 R124 R125 R126 R127 R128 R129 R130 R131 R132 R133 R134 R135 R136,10k,R_0805_2012Metric_Pad1.20x1.40mm_HandSolder,SMD:R 10k 1%,
1,J3,RPI5_40PIN,IDC-Header_2x20_P2.54mm_Vertical,2x20 2.54 mm shrouded box header + 40-way IDC ribbon,To Raspberry Pi 5 GPIO header (5 V pins deliberately not connected)
1,R11,1k,R_0805_2012Metric_Pad1.20x1.40mm_HandSolder,SMD:R 1k 1%,
1,D11,BLU,LED_0805_2012Metric_Pad1.15x1.40mm_HandSolder,0805 BLU LED,Software RUN (GPIO26)
2,U1 U3,MCP23017,SOIC-28W_7.5x17.9mm_P1.27mm,Microchip MCP23017-E/SO,"Outputs, I2C 0x20"
1,U2,ULN2803A,SOIC-18W_7.5x11.6mm_P1.27mm,TI ULN2803ADWR,Relay coil drivers
8,JP1 JP2 JP3 JP4 JP5 JP6 JP7 JP8,RAIL_SEL,SolderJumper-3_P1.3mm_Bridged12_RoundedPad1.0x1.5mm,,"Coil rail: 1-2 default (K1 = E-stop rail only, K2-K8 = E-stop + watchdog rail)"
8,D21 D22 D23 D24 D25 D26 D27 D28,RED,LED_0805_2012Metric_Pad1.15x1.40mm_HandSolder,0805 RED LED,K1 energised
1,J11,RELAY1,"PhoenixContact_MSTBA_2,5_3-G-5,08_1x03_P5.08mm_Horizontal","Phoenix 1757255 (MSTBA 2,5/3-G-5,08); plug 1757022",Relay 1 contacts COM/NO/NC
1,J12,RELAY2,"PhoenixContact_MSTBA_2,5_3-G-5,08_1x03_P5.08mm_Horizontal","Phoenix 1757255 (MSTBA 2,5/3-G-5,08); plug 1757022",Relay 2 contacts COM/NO/NC
1,J13,RELAY3,"PhoenixContact_MSTBA_2,5_3-G-5,08_1x03_P5.08mm_Horizontal","Phoenix 1757255 (MSTBA 2,5/3-G-5,08); plug 1757022",Relay 3 contacts COM/NO/NC
1,J14,RELAY4,"PhoenixContact_MSTBA_2,5_3-G-5,08_1x03_P5.08mm_Horizontal","Phoenix 1757255 (MSTBA 2,5/3-G-5,08); plug 1757022",Relay 4 contacts COM/NO/NC
1,J15,RELAY5,"PhoenixContact_MSTBA_2,5_3-G-5,08_1x03_P5.08mm_Horizontal","Phoenix 1757255 (MSTBA 2,5/3-G-5,08); plug 1757022",Relay 5 contacts COM/NO/NC
1,J16,RELAY6,"PhoenixContact_MSTBA_2,5_3-G-5,08_1x03_P5.08mm_Horizontal","Phoenix 1757255 (MSTBA 2,5/3-G-5,08); plug 1757022",Relay 6 contacts COM/NO/NC
1,J17,RELAY7,"PhoenixContact_MSTBA_2,5_3-G-5,08_1x03_P5.08mm_Horizontal","Phoenix 1757255 (MSTBA 2,5/3-G-5,08); plug 1757022",Relay 7 contacts COM/NO/NC
1,J18,RELAY8,"PhoenixContact_MSTBA_2,5_3-G-5,08_1x03_P5.08mm_Horizontal","Phoenix 1757255 (MSTBA 2,5/3-G-5,08); plug 1757022",Relay 8 contacts COM/NO/NC
8,D31 D32 D33 D34 D35 D36 D37 D38,SS14,D_SMA,SS14 (1 A 40 V Schottky),Solenoid flyback
1,J21,SOL1-2,"PhoenixContact_MC_1,5_4-G-3.5_1x04_P3.50mm_Horizontal",Phoenix 1844236; plug 1840382,"Solenoid outputs 1,2 (+24V, OUT-)"
1,J22,SOL3-4,"PhoenixContact_MC_1,5_4-G-3.5_1x04_P3.50mm_Horizontal",Phoenix 1844236; plug 1840382,"Solenoid outputs 3,4 (+24V, OUT-)"
1,J23,SOL5-6,"PhoenixContact_MC_1,5_4-G-3.5_1x04_P3.50mm_Horizontal",Phoenix 1844236; plug 1840382,"Solenoid outputs 5,6 (+24V, OUT-)"
1,J24,SOL7-8,"PhoenixContact_MC_1,5_4-G-3.5_1x04_P3.50mm_Horizontal",Phoenix 1844236; plug 1840382,"Solenoid outputs 7,8 (+24V, OUT-)"
1,J31,DI1-4,"PhoenixContact_MC_1,5_6-G-3.5_1x06_P3.50mm_Horizontal","Phoenix 1844252 (MC 1,5/6-G-3,5); plug 1840395",4 inputs + common + 24 V sensor supply
1,J32,DI5-8,"PhoenixContact_MC_1,5_6-G-3.5_1x06_P3.50mm_Horizontal","Phoenix 1844252 (MC 1,5/6-G-3,5); plug 1840395",4 inputs + common + 24 V sensor supply
1,J33,DI9-12,"PhoenixContact_MC_1,5_6-G-3.5_1x06_P3.50mm_Horizontal","Phoenix 1844252 (MC 1,5/6-G-3,5); plug 1840395",4 inputs + common + 24 V sensor supply
1,J34,DI13-16,"PhoenixContact_MC_1,5_6-G-3.5_1x06_P3.50mm_Horizontal","Phoenix 1844252 (MC 1,5/6-G-3,5); plug 1840395",4 inputs + common + 24 V sensor supply
2,U9 U10,ADS1115,TSSOP-10_3x3mm_P0.5mm,TI ADS1115IDGSR,"Gauges 1-4, I2C 0x48"
8,R141 R142 R143 R144 R145 R146 R147 R148,68k,R_0805_2012Metric_Pad1.20x1.40mm_HandSolder,SMD:R 68k 1%,0-10.5 V -> 0-2.57 V divider (top); AI1 = MechanicalVacuumPump gauge
8,R151 R152 R153 R154 R155 R156 R157 R158,22k,R_0805_2012Metric_Pad1.20x1.40mm_HandSolder,SMD:R 22k 1%,Divider bottom
1,J41,AI1-4,"PhoenixContact_MC_1,5_8-G-3.5_1x08_P3.50mm_Horizontal","Phoenix 1844265 (MC 1,5/8-G-3,5); plug 1840411",Analog in / AGND pairs
1,J42,AI5-8,"PhoenixContact_MC_1,5_8-G-3.5_1x08_P3.50mm_Horizontal","Phoenix 1844265 (MC 1,5/8-G-3,5); plug 1840411",Analog in / AGND pairs
1,U11,MAX3485,SOIC-8_3.9x4.9mm_P1.27mm,MAX3485ESA+ (or SP3485EN),"RS-485 half duplex, UART0 - multi-drop bus to the three turbo pump controllers"
2,R15 R16,680R,R_0805_2012Metric_Pad1.20x1.40mm_HandSolder,SMD:R 680R 1%,Fail-safe bias
1,R17,120R,R_0805_2012Metric_Pad1.20x1.40mm_HandSolder,SMD:R 120R 1%,
1,JP9,TERM,SolderJumper-2_P1.3mm_Open_RoundedPad1.0x1.5mm,,Bridge for 120R termination
2,D12 D13,SMAJ12CA,D_SMA,SMAJ12CA,
1,J4,RS485,"PhoenixContact_MC_1,5_3-G-3.5_1x03_P3.50mm_Horizontal",Phoenix 1844223; plug 1840379,RS-485 A/B/GND
1,U12,MAX3232,SOIC-16_3.9x9.9mm_P1.27mm,TI MAX3232ECDR,"RS-232, UART4"
1,J5,RS232,"PhoenixContact_MC_1,5_3-G-3.5_1x03_P3.50mm_Horizontal",Phoenix 1844223; plug 1840379,RS-232 TXD(out)/RXD(in)/GND
